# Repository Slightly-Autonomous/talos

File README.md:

# Talos

An open-source, **local-first spatial security and automation platform** for houses and other properties.

- Modular battery/solar sensor nodes: an ESP32-H2-class controller with four coplanar sensor-module slots.
- A local hub that owns all events, state, rules and commands, and works without internet.
- A deterministic digital twin that runs the real production logic in CI.
- A website (PWA first). Optional cloud and observability are never in the alarm path.

> **Status: Phase 8 started (hardware bring-up prep).** Contracts, domain core, an L1 twin (29 scenarios), `talos_hub` (SQLite journal, HTTP API with live events, token auth, optional Supabase copy, Docker/Railway deploys), and a website with live floor plan, replay, engineering, simulation, plus layout and rule editors over versioned, journaled configuration, backed by browser E2E; portable device firmware (drivers, debounce, retry, power admission, A/B OTA) tested on a register-level virtual board against the real hub, and compiled for ESP32-H2 in CI; CoAP device ingress with HMAC-authenticated frames, Ed25519-signed OTA campaigns delivered end to end to virtual nodes, device health projection, metrics and an optional Prometheus/Grafana profile; Supabase sign-in, an MCP server for AI assistants (policy-capped, no unlock/disarm), a webhook notifier and a Frigate NVR connector; a dev-kit bring-up guide, HIL test suite and manufacturing release checklist ready for the first real hardware. Nothing has run on real hardware or a real Thread network yet. See [roadmap](#roadmap). Everything is experimental and is not a certified alarm or life-safety system.

## Quick start

Prerequisites: [bazelisk](https://github.com/bazelbuild/bazelisk), a C++20 compiler (Apple clang 17 / GCC 13+), Node ≥ 20.19 and pnpm 10.

```bash
bazel test //...                    # all C++ tests
```

```bash
bazel test --config=asan //...      # under AddressSanitizer (also: --config=ubsan)
```

```bash
pnpm install && pnpm ts:check       # proto codegen + all TS typecheck/tests + web lint/build
```

```bash
pnpm proto:lint                     # buf lint on contracts/proto
```

```bash
bazel run //server:talos_hub -- --config $PWD/deploy/config/hub.dev.yaml   # then: curl localhost:8080/v1/health
```

See [`deploy/README.md`](deploy/README.md) for Docker Compose, Supabase and Railway.

Run the website against that hub, with virtual devices (log in with `dev-owner-token`):

```bash
pnpm --filter @talos/devsim start
```

```bash
pnpm -C web dev                     # http://localhost:5173
```

```bash
pnpm -C web e2e                     # browser E2E: boots hub + devsim + web itself
```

```bash
bazel run //simulation/runner:talos_sim -- $PWD/simulation/scenarios/scenarios/backyard_intrusion_at_2am.yaml --root $PWD/simulation/scenarios
```

## Repository map
| Path | What |
|---|---|
| `contracts/proto/talos/v1` | Protobuf contracts (the wire/storage schema) |
| `contracts/manifests` | Sample board/module/property YAML. **All numbers provisional** |
| `core/` | Pure C++20 domain core: journal, ingest/dedup, state/replay, commands, policy, rules, manifest validator |
| `codec/` | Proto ↔ core mapping and the YAML loader |
| `simulation/` | Digital twin: world, virtual devices/transport, scenario runner, scenario corpus |
| `server/` | `talos_hub`: SQLite journal, HTTP API v1 + SSE, auth, config switches |
| `packages/contracts` | Generated TypeScript contracts and typed `HubClient` |
| `connectors/supabase_sync` | Optional read-only Supabase copy |
| `connectors/mcp_server` | MCP server for AI assistants (agent principal, policy-capped) |
| `connectors/webhook_notifier` | `notify` commands → ntfy/JSON webhooks |
| `connectors/frigate` | Frigate NVR detections → camera observations |
| `deploy/` | Dev config, Docker Compose, Railway templates, Supabase migrations |
| `web/` | React + TypeScript website: live floor plan, replay, engineering, simulation (Playwright E2E) |
| `tools/devsim` | Virtual devices for the dev property, over the hub's device API |
| `docs/` | Architecture, ADRs, open decisions, security invariants, requirements, original spec |
| `firmware/` | Portable device firmware, virtual board (L2 twin), ESP32-H2 project |
| `common/` | Shared portable code (SHA-256/HMAC, CoAP codec) |
| `hardware/` | Provisional BOMs (dev-kit rig, mainboard candidates); KiCad later |
| `tests/hil/` | Hardware-in-the-loop tests (pytest-embedded, manual workflow) |
| `observability/` | Placeholder (profile lives in `deploy/observability`) |

API reference: [`docs/api.md`](docs/api.md). Start with [`docs/architecture/overview.md`](docs/architecture/overview.md) and [`docs/decisions/`](docs/decisions/README.md).

## Roadmap
0–1. Repo, contracts, deterministic core
2. Deterministic L1 digital twin and scenario runner
3. Local hub: SQLite journal, API, auth
4. Website: live state, replay; 4b: versioned config, layout and rule editors
5. Portable firmware on virtual hardware, then ESP-IDF
6. Thread/CoAP, OTA, observability, hardening
7. Optional Supabase/Railway, MCP connector
8. Dev-board validation, custom PCB, manufacturing ← *here* (needs real hardware)

## License
Apache-2.0. See [LICENSE](LICENSE).

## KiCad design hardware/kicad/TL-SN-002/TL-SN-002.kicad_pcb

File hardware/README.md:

# hardware

The Talos custom-hardware workstream. It follows `TALOS_CUSTOM_HARDWARE_HANDOFF_v0_1` (milestones H0–H7). Root ADRs in `docs/decisions/` still win over anything here (ADR 0017 links the two).

> **Nothing in this folder is a validated design.** The schematics pass ERC and the autorouted layouts pass DRC, but no electrical engineer has reviewed them, and nothing has been built or measured. **Do not order boards** until the review items in [layout/README.md](layout/README.md) are closed (HW-0005). Every value is `provisional: true` until a bench measurement says otherwise.

## Boards

| ID | What | Bespoke? | State |
|---|---|---|---|
| TL-HUB-REF | Hub: Pi 5 / mini-PC + USB 802.15.4 RCP | No, bought | `bom/devkit_rig_v0.csv` |
| TL-SN-002 | Self-contained Thread Sensor Node: ESP32-H2, Hall + accel + T/RH + PIR, 2 × AA or USB-C, 10 lamps, 3 buttons (ADR 0019) | Yes | Schematic + routed 2-layer layout, 0 DRC errors, not yet reviewed |
| TL-SN-001, TL-MOD-001..004, TL-TEST-001 | The four-slot modular node and its cards | – | **Archived** 2026-11-22: [archive/modular-2026-11](archive/modular-2026-11/README.md) (git tag `modular-checkpoint-2026-11`) |
| TL-DBG-001 | One-slot USB debug adapter: one sensor_edge_v1 board on a PC, kept active for future sensor boards (MCP2221A bridge, PPK2 meter headers) | Yes, bench tool | Schematic + routed 2-layer layout, 0 DRC errors ([HW-0007](architecture/decisions/0007-slot-socket-and-debug-adapter.md)) |
| TL-VN-001 | Vision Node (separate board, CM4/CM5/video SoC) | Yes | H5 study not started; manifest only |

The camera **slot** module (`smart_camera_s3_v1`) is superseded by TL-VN-001 ([ADR HW-0001](architecture/decisions/0001-hardware-family.md)).

## Where things are

| Path | Contents |
|---|---|
| `architecture/` | [hardware-overview.md](architecture/hardware-overview.md) and hardware ADRs HW-0001..0006 |
| `requirements/` | Requirements (`hardware-requirements.yaml`), decision/risk register, datasheet register, component selection, interface test matrix |
| `interfaces/` | [sensor_edge_v1](interfaces/sensor_edge_v1.md) slot connector contract |
| `pins/` | Complete ESP32-H2-MINI-1 pad ledger (CSV), the single source for the firmware `BoardSupport` table |
| `budgets/` | Per-slot and board resource budget (CSV) |
| `power/` | Power-tree study and operating-mode matrix (H2) |
| `mechanical/` | Connector shortlist and mechanical notes |
| `kicad/` | KiCad 10 projects, all **generated** by `scripts/gen_schematics.py`; project-local symbols in `kicad/libraries/` |
| `scripts/` | Schematic generator, ERC/netlist checks, power-budget calculator |
| `results/` | Captured tool output (ERC/DRC summary, netlist comparison, power report), dated and versioned |
| `layout/` | H4 layout method, board summary and the pre-order review list |
| `fab/` | Prototype fabrication packages (Gerbers, drill, CPL, BOM, renders), for quotes and DFM only |
| `templates/` | Component evaluation template |
| `bom/` | Dev-kit rig BOM (bring-up path, ADR 0016) |

Board and module manifests live in `contracts/manifests/` (one schema, validated by `core/manifest`). `sensor_node_proto_a.yaml` must agree with `pins/esp32h2_mini1_pin_ledger.csv` and `firmware/esp_idf/main/board_tl_sn_001.h`.

## Reproduce

```bash
# KiCad 10.0.x: kicad-cli on PATH, or set KICAD_CLI.
python3 hardware/scripts/gen_schematics.py          # regenerate all projects
python3 hardware/scripts/check_kicad.py --pdf      # ERC + netlist round-trip + PDFs -> hardware/results/
python3 hardware/scripts/power_budget.py             # H2 calculations -> hardware/results/power-budget.md
bazel test //core/manifest:manifest_test //codec:yaml_loader_test   # manifest validator (HW-MF tests)
```

## Hard rules
- Do not order parts or boards, request binding quotes, create factory keys or burn eFuses without explicit owner approval.
- Never hand-edit a generated `.kicad_sch`. Change the generator, regenerate, and re-run the checks.
- A green ERC is not "validated". See `requirements/design-risks.md` for what still needs a reviewer or a bench.

Vendor drawings marked proprietary (e.g. Samtec's HSEC8 prints) live in `hardware/vendor-docs/`, which git ignores. Re-download them from the vendor site; the register in `requirements/datasheet-register.md` names each one.

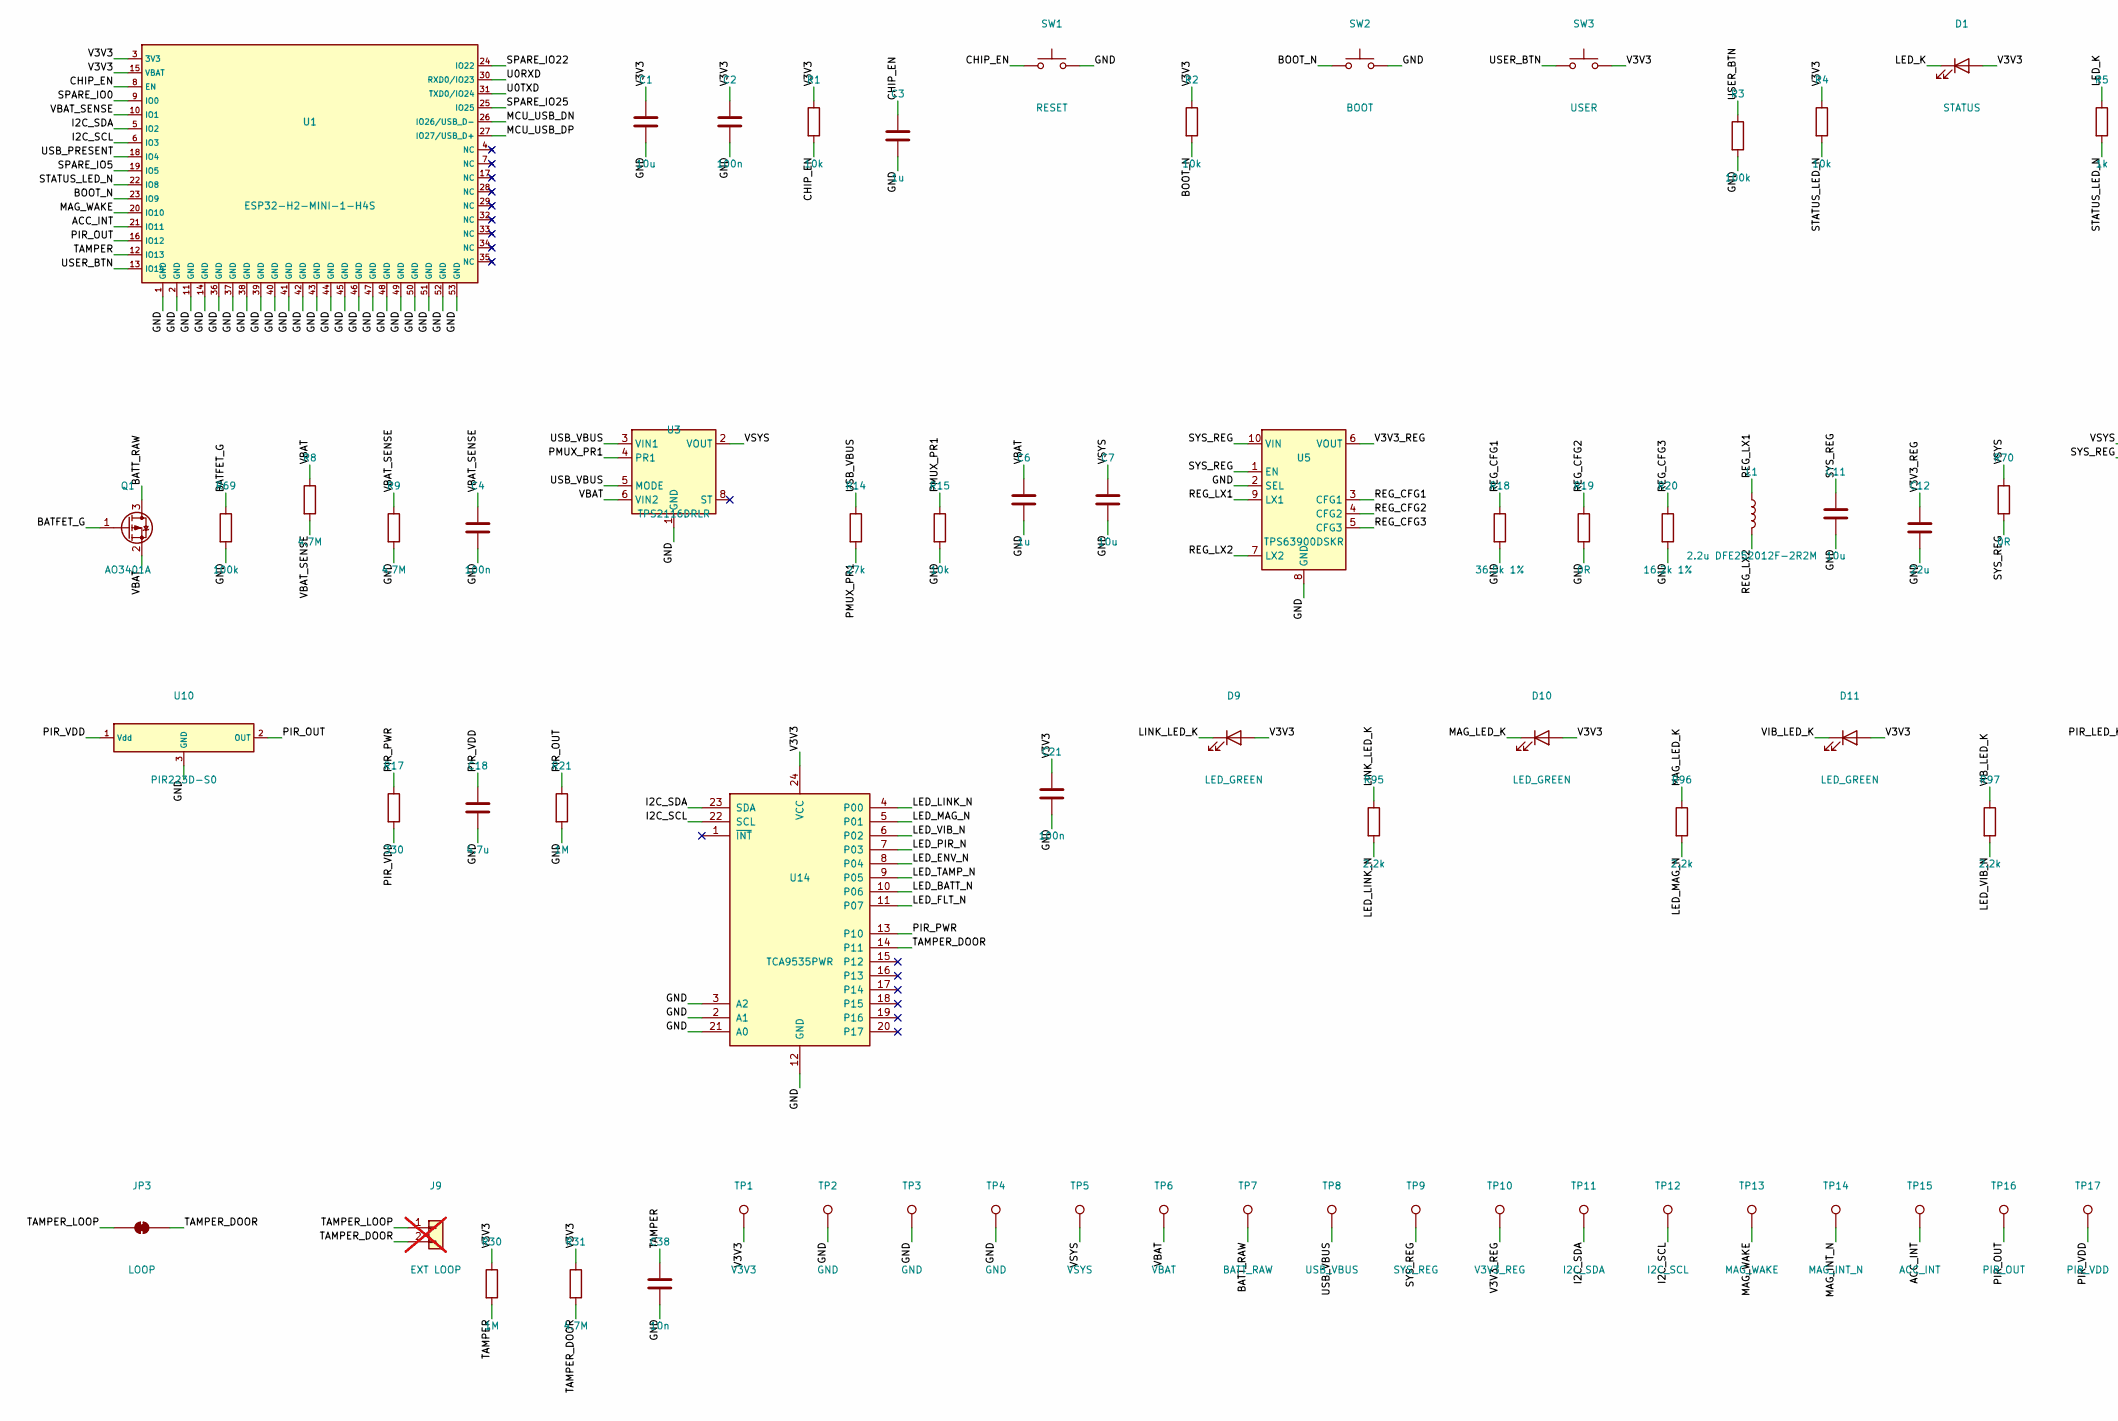
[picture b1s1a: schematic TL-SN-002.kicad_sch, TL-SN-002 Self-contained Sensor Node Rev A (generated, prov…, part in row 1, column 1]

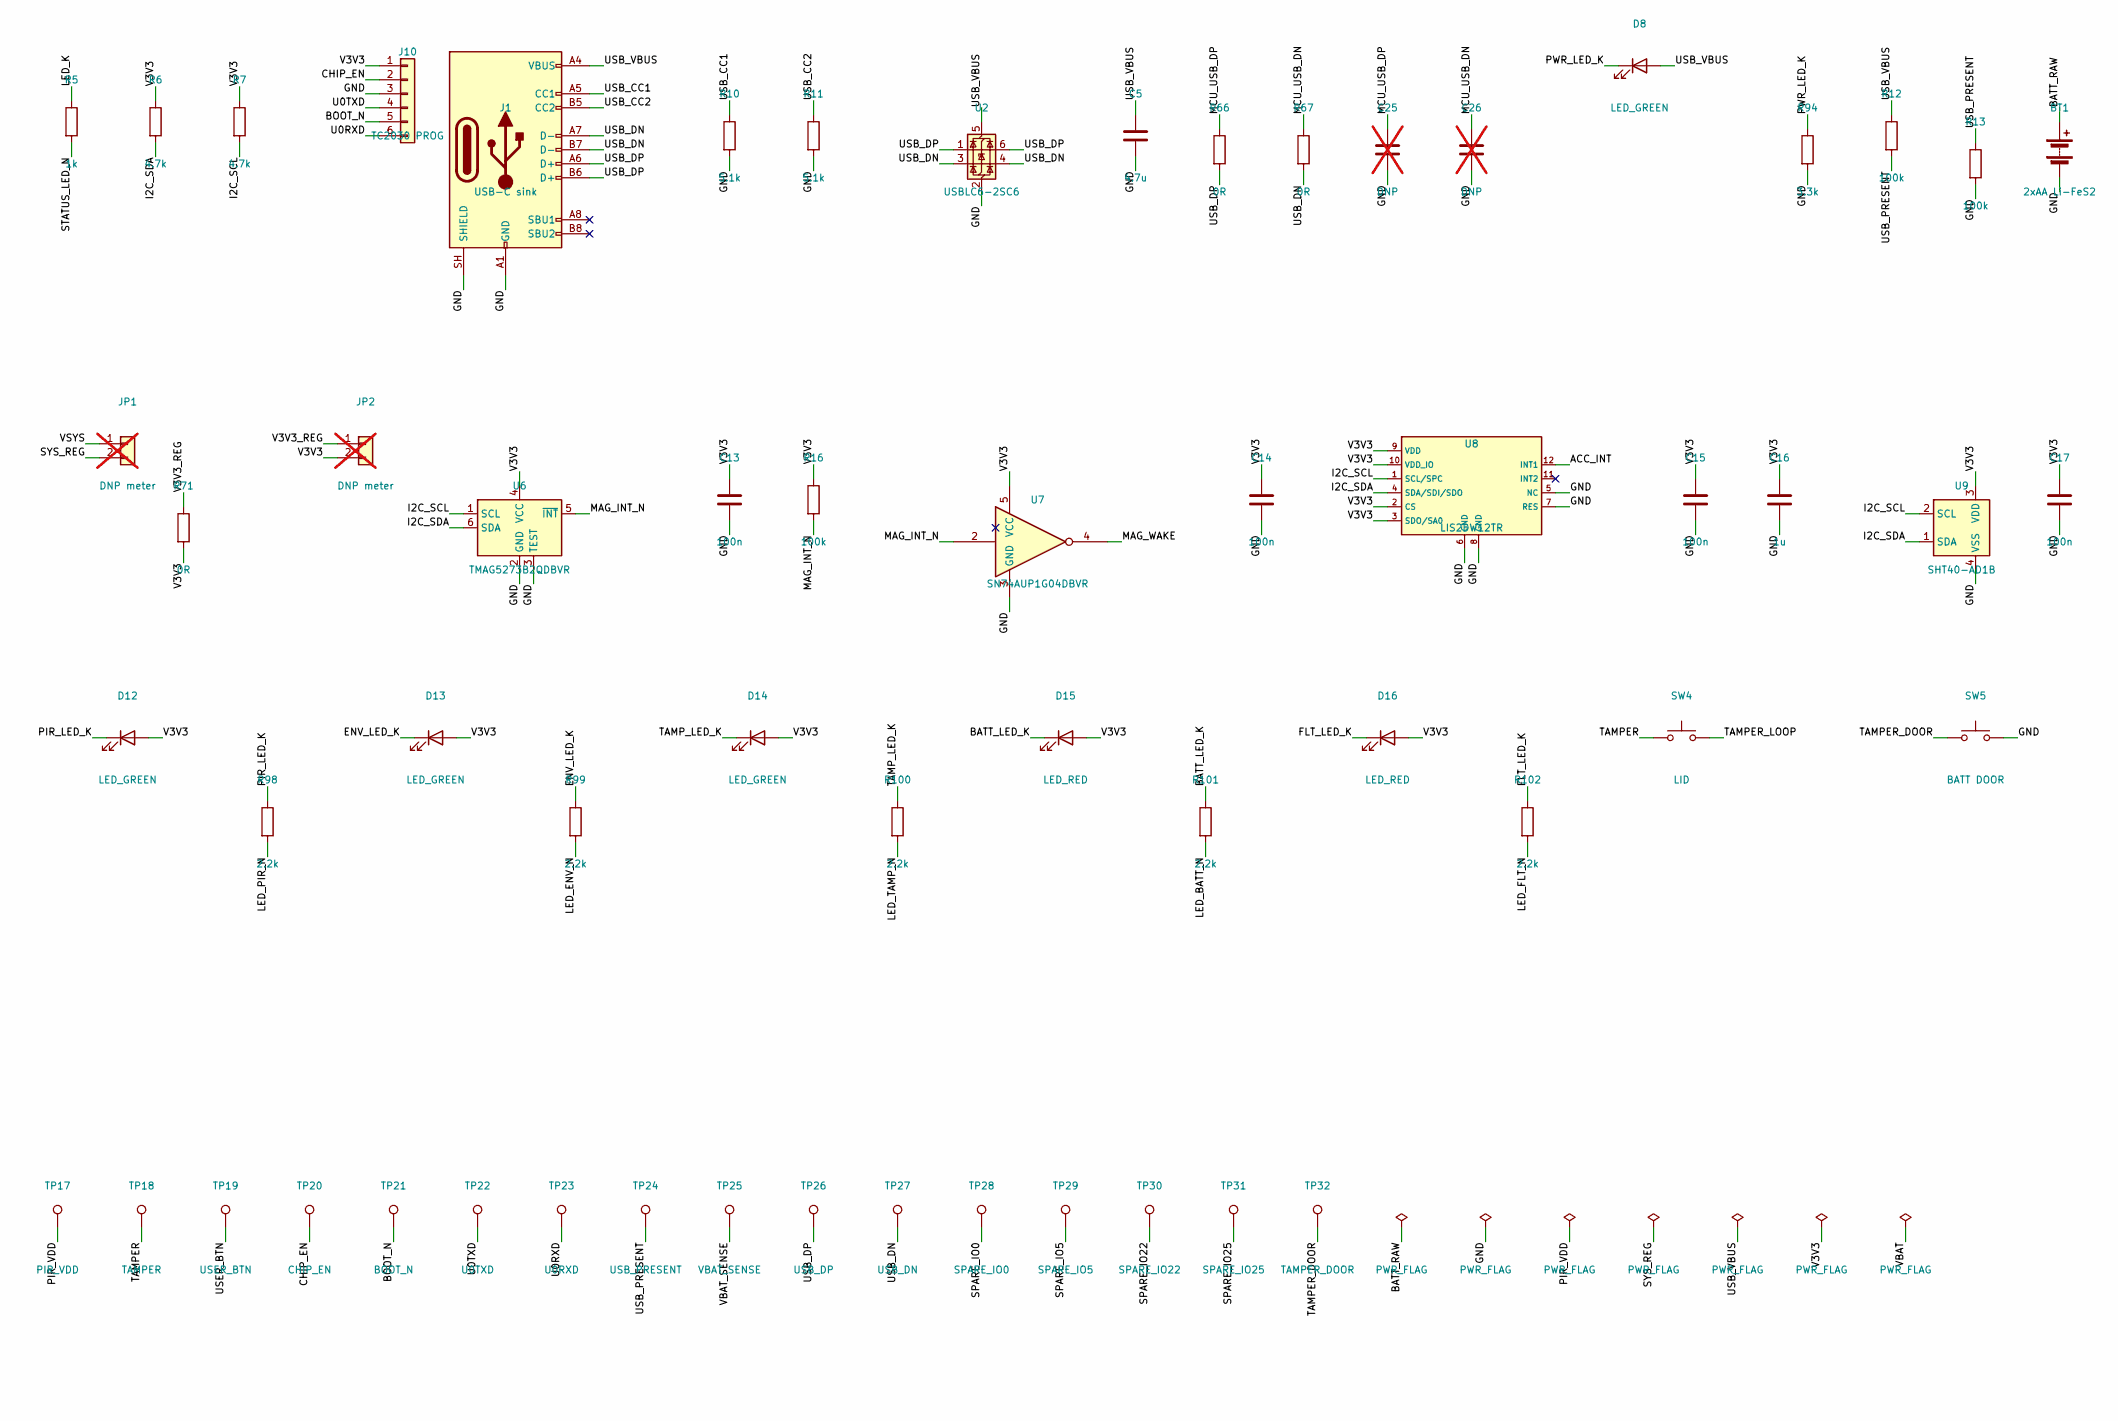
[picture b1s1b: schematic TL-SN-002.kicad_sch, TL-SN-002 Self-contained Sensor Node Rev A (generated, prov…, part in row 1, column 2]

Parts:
BT1: 2xAA Li-FeS2; BatteryHolder_Keystone_2462_2xAA
C1, C7, C11: 10u; C_0805_2012Metric
C2, C4, C13, C14, C15, C17, C21: 100n; C_0402_1005Metric
C3, C6, C16: 1u; C_0402_1005Metric
C5, C18: 4.7u; C_0805_2012Metric
C12: 22u; C_0805_2012Metric
C25, C26: DNP; C_0402_1005Metric; not fitted
C38: 10n; C_0402_1005Metric
D1: STATUS; LED_0603_1608Metric
D8, D9, D10, D11, D12, D13, D14: LED_GREEN; LED_0603_1608Metric
D15, D16: LED_RED; LED_0603_1608Metric
J1: USB-C sink; USB_C_Receptacle_GCT_USB4105-xx-A_16P_TopMnt_Horizontal
J9: EXT LOOP; JST_PH_S2B-PH-SM4-TB_1x02-1MP_P2.00mm_Horizontal; not fitted
J10: TC2030 PROG; Tag-Connect_TC2030-IDC-NL_2x03_P1.27mm_Vertical
JP1, JP2: DNP meter; PinHeader_1x02_P2.54mm_Vertical; not fitted
JP3: LOOP; SolderJumper-2_P1.3mm_Bridged_RoundedPad1.0x1.5mm
L1: 2.2u DFE252012F-2R2M; L_1008_2520Metric
Q1: AO3401A; SOT-23
R1, R2, R4, R15: 10k; R_0402_1005Metric
R3, R12, R13, R16, R69: 100k; R_0402_1005Metric
R5: 1k; R_0402_1005Metric
R6, R7: 4.7k; R_0402_1005Metric
R8, R9, R31: 4.7M; R_0402_1005Metric
R10, R11: 5.1k; R_0402_1005Metric
R14: 27k; R_0402_1005Metric
R17: 330; R_0402_1005Metric
R18: 36.5k 1%; R_0402_1005Metric
R19, R66, R67: 0R; R_0402_1005Metric
R20: 16.2k 1%; R_0402_1005Metric
R21, R30: 1M; R_0402_1005Metric
R70, R71: 0R; R_0805_2012Metric
R94: 3.3k; R_0402_1005Metric
R95, R96, R97, R98, R99, R100, R101, R102: 2.2k; R_0402_1005Metric
SW1: RESET; SW_SPST_PTS810
SW2: BOOT; SW_SPST_PTS810
SW3: USER; SW_SPST_PTS810
SW4: LID; SW_Push_1P1T_XKB_TS-1187A
SW5: BATT DOOR; SW_Push_1P1T_XKB_TS-1187A
TP1: V3V3; TestPoint_Pad_D1.0mm
TP2, TP3, TP4: GND; TestPoint_Pad_D1.0mm
TP5: VSYS; TestPoint_Pad_D1.0mm
TP6: VBAT; TestPoint_Pad_D1.0mm
TP7: BATT_RAW; TestPoint_Pad_D1.0mm
TP8: USB_VBUS; TestPoint_Pad_D1.0mm
TP9: SYS_REG; TestPoint_Pad_D1.0mm
TP10: V3V3_REG; TestPoint_Pad_D1.0mm
TP11: I2C_SDA; TestPoint_Pad_D1.0mm
TP12: I2C_SCL; TestPoint_Pad_D1.0mm
TP13: MAG_WAKE; TestPoint_Pad_D1.0mm
TP14: MAG_INT_N; TestPoint_Pad_D1.0mm
TP15: ACC_INT; TestPoint_Pad_D1.0mm
TP16: PIR_OUT; TestPoint_Pad_D1.0mm
TP17: PIR_VDD; TestPoint_Pad_D1.0mm
TP18: TAMPER; TestPoint_Pad_D1.0mm
TP19: USER_BTN; TestPoint_Pad_D1.0mm
TP20: CHIP_EN; TestPoint_Pad_D1.0mm
TP21: BOOT_N; TestPoint_Pad_D1.0mm
TP22: U0TXD; TestPoint_Pad_D1.0mm
TP23: U0RXD; TestPoint_Pad_D1.0mm
TP24: USB_PRESENT; TestPoint_Pad_D1.0mm
TP25: VBAT_SENSE; TestPoint_Pad_D1.0mm
TP26: USB_DP; TestPoint_Pad_D1.0mm
TP27: USB_DN; TestPoint_Pad_D1.0mm
TP28: SPARE_IO0; TestPoint_Pad_D1.0mm
TP29: SPARE_IO5; TestPoint_Pad_D1.0mm
TP30: SPARE_IO22; TestPoint_Pad_D1.0mm
TP31: SPARE_IO25; TestPoint_Pad_D1.0mm
TP32: TAMPER_DOOR; TestPoint_Pad_D1.0mm
U1: ESP32-H2-MINI-1-H4S; ESP32-H2-MINI-1
U2: USBLC6-2SC6; SOT-23-6
U3: TPS2116DRLR; SOT-583-8
U5: TPS63900DSKR; WSON-10-1EP_2.5x2.5mm_P0.5mm_EP1.2x2mm
U6: TMAG5273B2QDBVR; SOT-23-6
U7: SN74AUP1G04DBVR; SOT-23-5
U8: LIS2DW12TR; LGA-12_2x2mm_P0.5mm
U9: SHT40-AD1B; Sensirion_DFN-4_1.5x1.5mm_P0.8mm_SHT4x_CentralKeepout
U10: PIR223D-S0; PIR_NEWOPTO_PIR223D_TO-5
U14: TCA9535PWR; TSSOP-24_4.4x7.8mm_P0.65mm

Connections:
/ACC_INT: TP15.1, U1.21 (IO11), U8.12 (INT1)
/BATFET_G: Q1.1 (G), R69.1
/BATT_LED_K: D15.1 (K), R101.1
/BATT_RAW: BT1.1 (+), Q1.3 (D), TP7.1
/BOOT_N: J10.5, R2.2, SW2.1, TP21.1, U1.23 (IO9)
/CHIP_EN: C3.1, J10.2, R1.2, SW1.1, TP20.1, U1.8 (EN)
/ENV_LED_K: D13.1 (K), R99.1
/FLT_LED_K: D16.1 (K), R102.1
/GND: BT1.2 (-), C1.2, C2.2, C3.2, C4.2, C5.2, C6.2, C7.2, C11.2, C12.2, C13.2, C14.2, C15.2, C16.2, C17.2, C18.2, C21.2, C25.2, C26.2, C38.2, J1.A1 (GND), J1.A12 (GND), J1.B1 (GND), J1.B12 (GND), J1.SH (SHIELD), J10.3, R3.2, R9.2, R10.2, R11.2, R13.2, R15.2, R18.2, R19.2, R20.2, R21.2, R69.2, R94.2, SW1.2, SW2.2, SW5.2, TP2.1, TP3.1, TP4.1, U1.1 (GND), U1.2 (GND), U1.11 (GND), U1.14 (GND), U1.36 (GND), U1.37 (GND), U1.38 (GND), U1.39 (GND), U1.40 (GND), U1.41 (GND), U1.42 (GND), U1.43 (GND), U1.44 (GND), U1.45 (GND), U1.46 (GND), U1.47 (GND), U1.48 (GND), U1.49 (GND), U1.50 (GND), U1.51 (GND), U1.52 (GND), U1.53 (GND), U2.2 (GND), U3.1 (GND), U5.2 (SEL), U5.8 (GND), U5.11 (GND), U6.2 (GND), U6.3 (TEST), U7.3 (GND), U8.5 (NC), U8.6 (GND), U8.7 (RES), U8.8 (GND), U9.4 (VSS), U10.3 (GND), U14.2 (A1), U14.3 (A2), U14.12 (GND), U14.21 (A0)
/I2C_SCL: R7.2, TP12.1, U1.6 (IO3), U6.1 (SCL), U8.1 (SCL/SPC), U9.2 (SCL), U14.22 (SCL)
/I2C_SDA: R6.2, TP11.1, U1.5 (IO2), U6.6 (SDA), U8.4 (SDA/SDI/SDO), U9.1 (SDA), U14.23 (SDA)
/LED_BATT_N: R101.2, U14.10 (P06)
/LED_ENV_N: R99.2, U14.8 (P04)
/LED_FLT_N: R102.2, U14.11 (P07)
/LED_K: D1.1 (K), R5.1
/LED_LINK_N: R95.2, U14.4 (P00)
/LED_MAG_N: R96.2, U14.5 (P01)
/LED_PIR_N: R98.2, U14.7 (P03)
/LED_TAMP_N: R100.2, U14.9 (P05)
/LED_VIB_N: R97.2, U14.6 (P02)
/LINK_LED_K: D9.1 (K), R95.1
/MAG_INT_N: R16.2, TP14.1, U6.5 (~INT), U7.2
/MAG_LED_K: D10.1 (K), R96.1
/MAG_WAKE: TP13.1, U1.20 (IO10), U7.4
/MCU_USB_DN: C26.1, R67.1, U1.26 (IO26/USB_D-)
/MCU_USB_DP: C25.1, R66.1, U1.27 (IO27/USB_D+)
/PIR_LED_K: D12.1 (K), R98.1
/PIR_OUT: R21.1, TP16.1, U1.16 (IO12), U10.2 (OUT)
/PIR_PWR: R17.1, U14.13 (P10)
/PIR_VDD: C18.1, R17.2, TP17.1, U10.1 (Vdd)
/PMUX_PR1: R14.2, R15.1, U3.4 (PR1)
/PWR_LED_K: D8.1 (K), R94.1
/REG_CFG1: R18.1, U5.3 (CFG1)
/REG_CFG2: R19.1, U5.4 (CFG2)
/REG_CFG3: R20.1, U5.5 (CFG3)
/REG_LX1: L1.1, U5.9 (LX1)
/REG_LX2: L1.2, U5.7 (LX2)
/SPARE_IO0: TP28.1, U1.9 (IO0)
/SPARE_IO5: TP29.1, U1.19 (IO5)
/SPARE_IO22: TP30.1, U1.24 (IO22)
/SPARE_IO25: TP31.1, U1.25 (IO25)
/STATUS_LED_N: R4.2, R5.2, U1.22 (IO8)
/SYS_REG: C11.1, JP1.2, R70.2, TP9.1, U5.1 (EN), U5.10 (VIN)
/TAMPER: C38.1, R30.2, SW4.1, TP18.1, U1.12 (IO13)
/TAMPER_DOOR: J9.2, JP3.2 (B), R31.2, SW5.1, TP32.1, U14.14 (P11)
/TAMPER_LOOP: J9.1, JP3.1 (A), SW4.2
/TAMP_LED_K: D14.1 (K), R100.1
/U0RXD: J10.6, TP23.1, U1.30 (RXD0/IO23)
/U0TXD: J10.4, TP22.1, U1.31 (TXD0/IO24)
/USB_CC1: J1.A5 (CC1), R10.1
/USB_CC2: J1.B5 (CC2), R11.1
/USB_DN: J1.A7 (D-), J1.B7 (D-), R67.2, TP27.1, U2.3 (I/O2), U2.4 (I/O2)
/USB_DP: J1.A6 (D+), J1.B6 (D+), R66.2, TP26.1, U2.1 (I/O1), U2.6 (I/O1)
/USB_PRESENT: R12.2, R13.1, TP24.1, U1.18 (IO4)
/USB_VBUS: C5.1, D8.2 (A), J1.A4 (VBUS), J1.A9 (VBUS), J1.B4 (VBUS), J1.B9 (VBUS), R12.1, R14.1, TP8.1, U2.5 (VBUS), U3.3 (VIN1), U3.5 (MODE)
/USER_BTN: R3.1, SW3.1, TP19.1, U1.13 (IO14)
/V3V3: C1.1, C2.1, C13.1, C14.1, C15.1, C16.1, C17.1, C21.1, D1.2 (A), D9.2 (A), D10.2 (A), D11.2 (A), D12.2 (A), D13.2 (A), D14.2 (A), D15.2 (A), D16.2 (A), J10.1, JP2.2, R1.1, R2.1, R4.1, R6.1, R7.1, R16.1, R30.1, R31.1, R71.2, SW3.2, TP1.1, U1.3 (3V3), U1.15 (VBAT), U6.4 (VCC), U7.5 (VCC), U8.2 (CS), U8.3 (SDO/SA0), U8.9 (VDD), U8.10 (VDD_IO), U9.3 (VDD), U14.24 (VCC)
/V3V3_REG: C12.1, JP2.1, R71.1, TP10.1, U5.6 (VOUT)
/VBAT: C6.1, Q1.2 (S), R8.1, TP6.1, U3.6 (VIN2)
/VBAT_SENSE: C4.1, R8.2, R9.1, TP25.1, U1.10 (IO1)
/VIB_LED_K: D11.1 (K), R97.1
/VSYS: C7.1, JP1.1, R70.1, TP5.1, U3.2 (VOUT), U3.7 (VOUT)

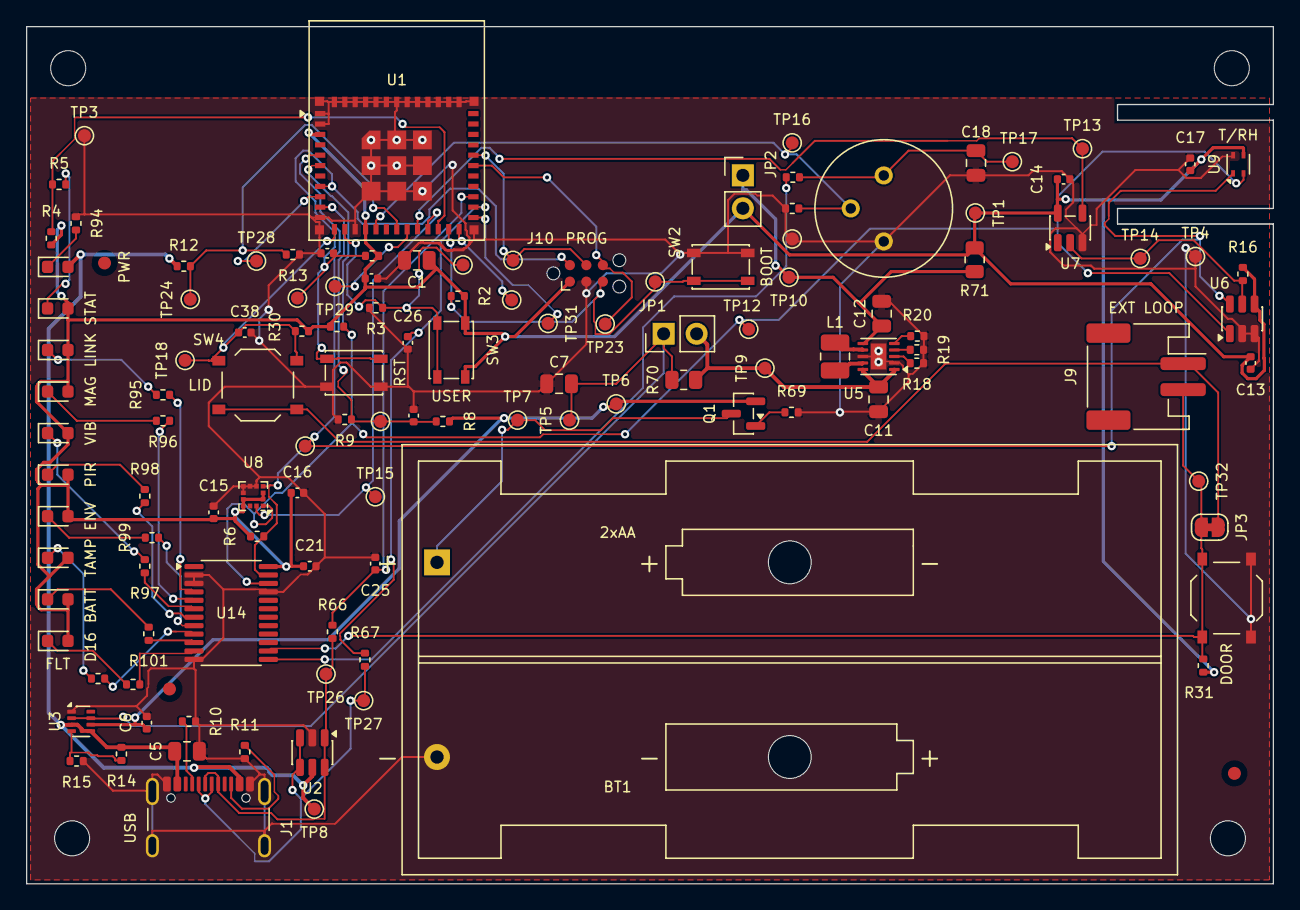
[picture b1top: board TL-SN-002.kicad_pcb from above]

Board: 2 copper layers, 96.0 x 66.0 mm, 129 parts (0 on the bottom side), 62 nets.

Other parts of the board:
FID1, FID2, FID3: fiducial; Fiducial_1mm_Mask2mm
H1, H2, H3, H4: mounting hole; MountingHole_2.7mm_M2.5

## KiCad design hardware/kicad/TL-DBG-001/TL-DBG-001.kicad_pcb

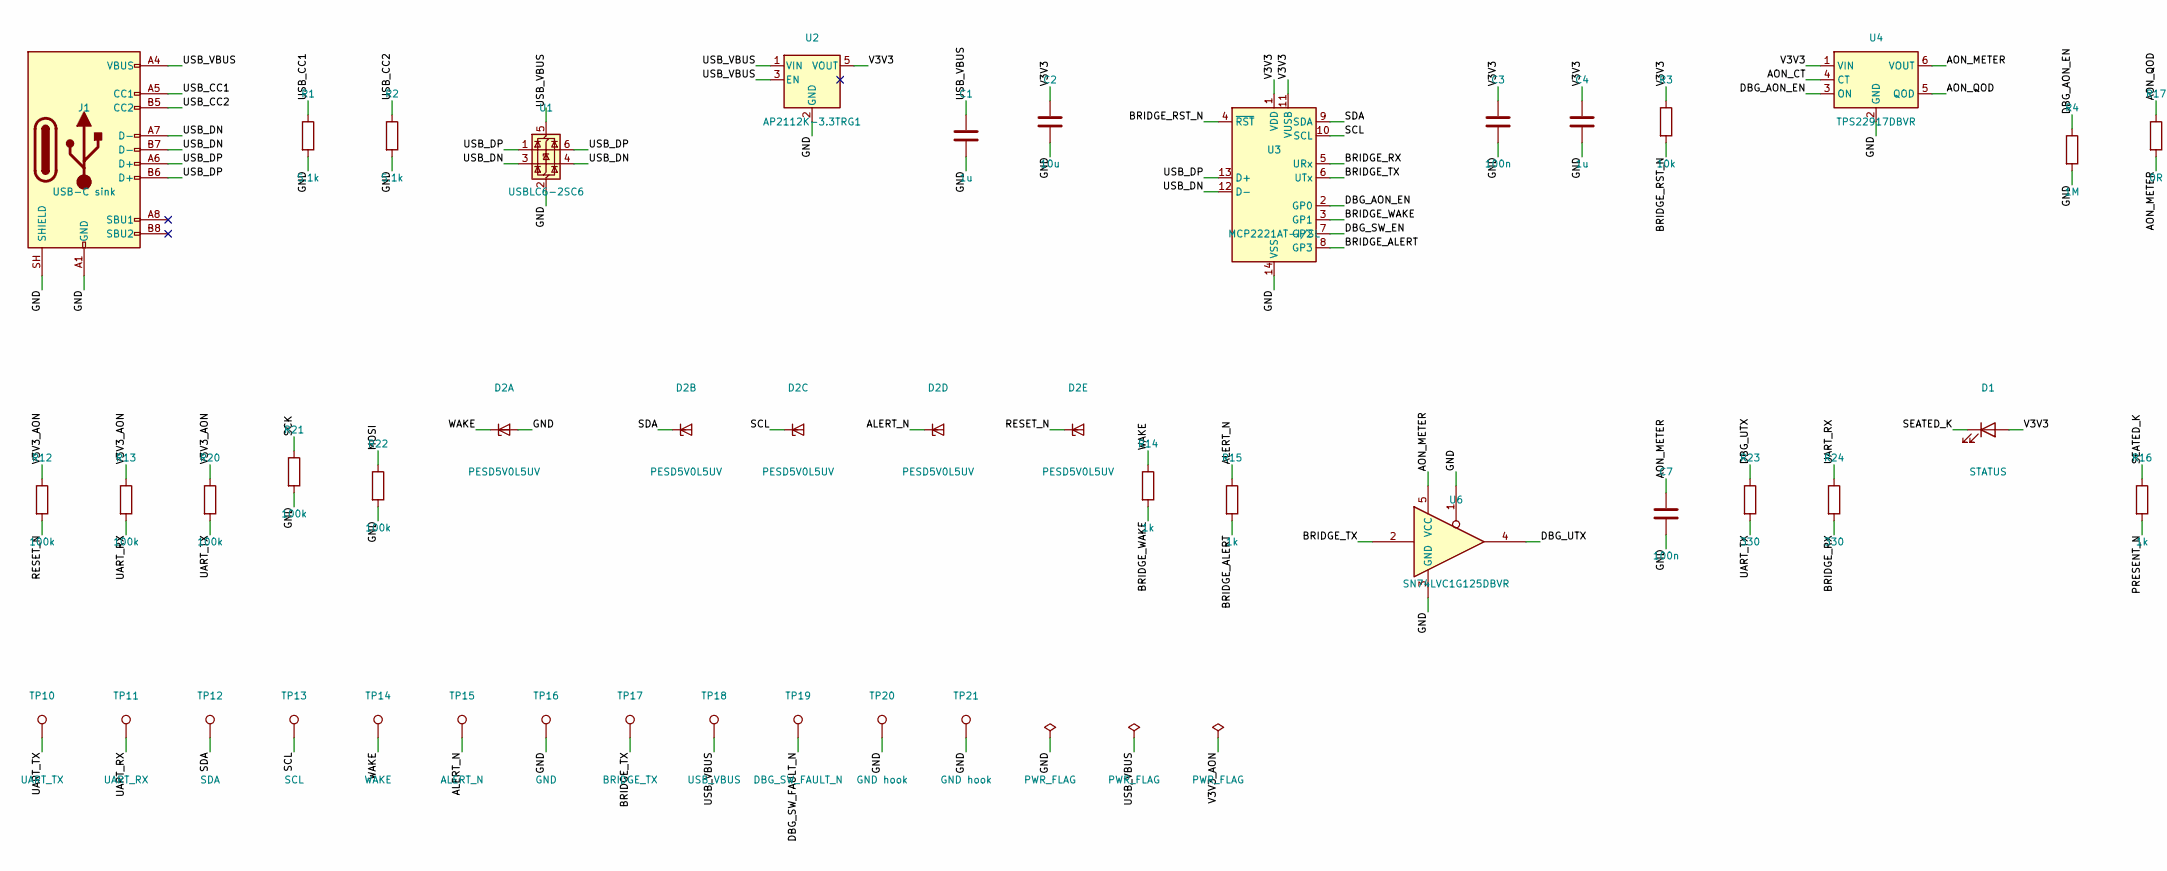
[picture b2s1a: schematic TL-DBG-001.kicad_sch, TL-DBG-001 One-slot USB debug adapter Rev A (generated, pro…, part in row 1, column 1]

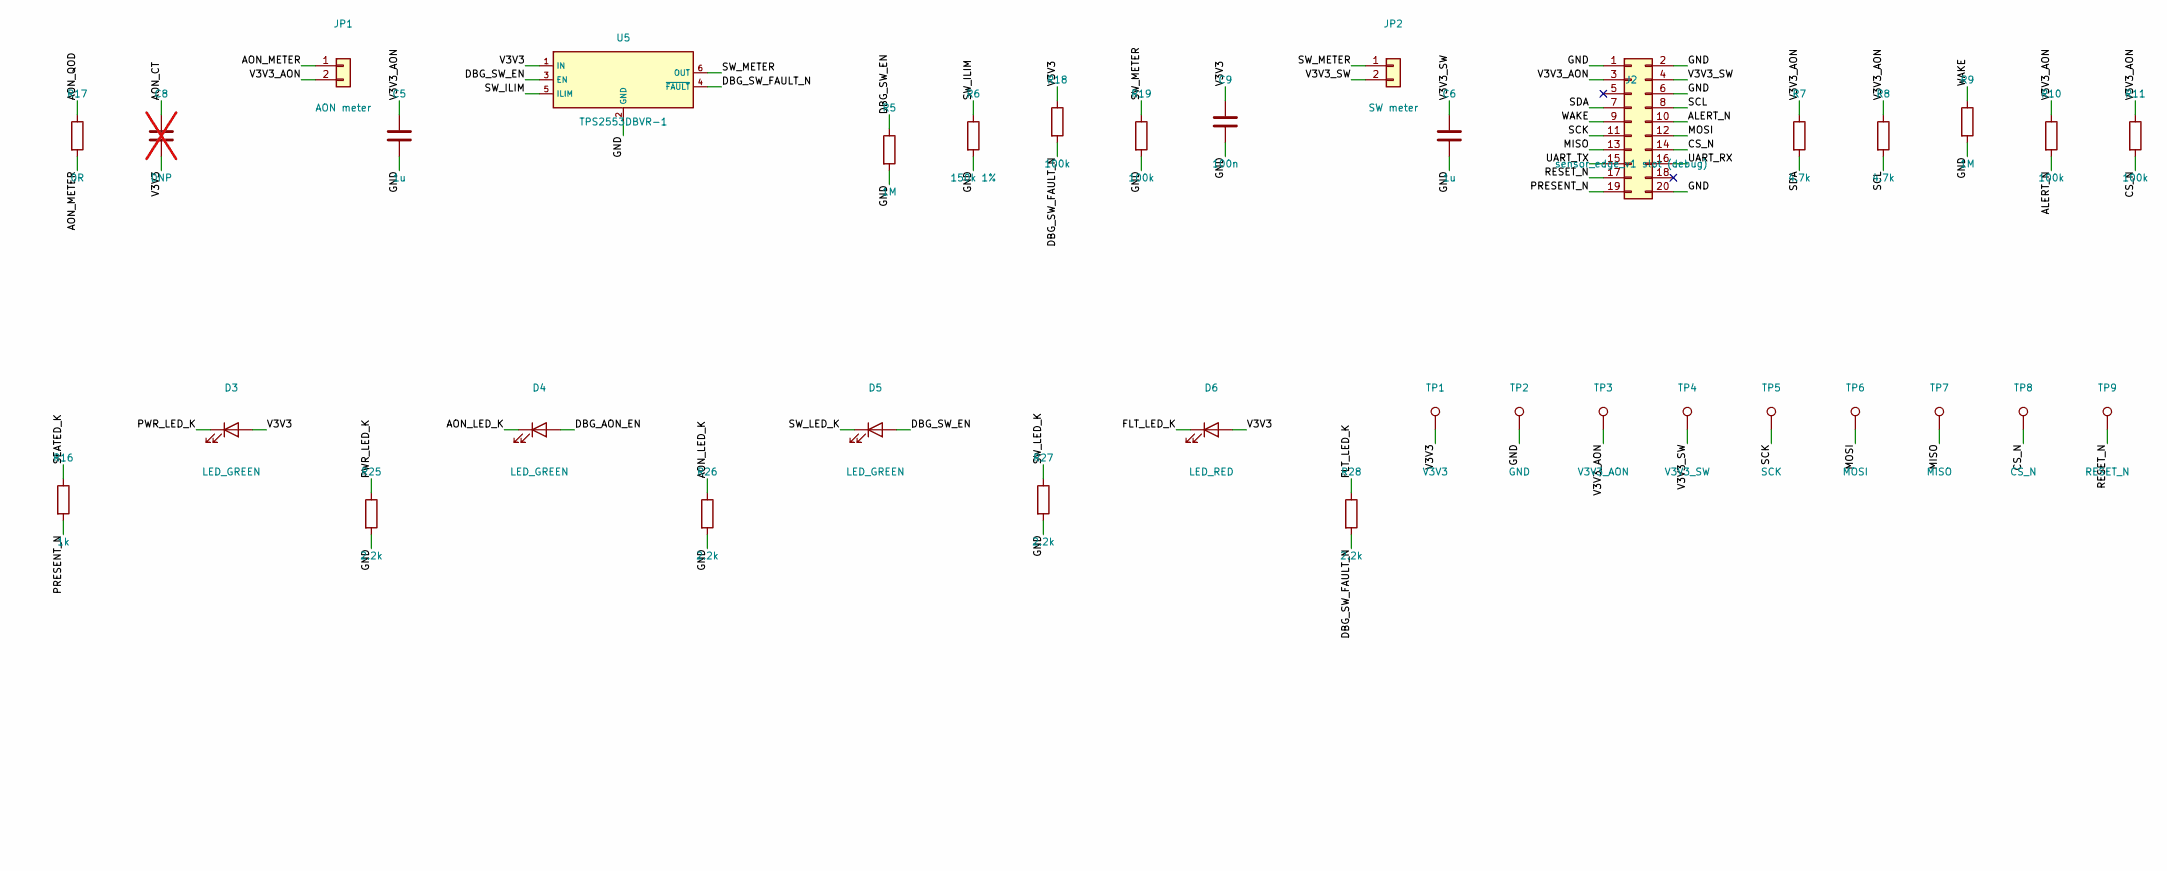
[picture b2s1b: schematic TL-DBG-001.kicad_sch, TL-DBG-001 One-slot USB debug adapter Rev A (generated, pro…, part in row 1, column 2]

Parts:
C1, C4, C5, C6: 1u; C_0402_1005Metric
C2: 10u; C_0805_2012Metric
C3, C7, C9: 100n; C_0402_1005Metric
C8: DNP; C_0402_1005Metric; not fitted
D1: STATUS; LED_0603_1608Metric
D2: PESD5V0L5UV; SOT-666
D3, D4, D5: LED_GREEN; LED_0603_1608Metric
D6: LED_RED; LED_0603_1608Metric
J1: USB-C sink; USB_C_Receptacle_GCT_USB4105-xx-A_16P_TopMnt_Horizontal
J2: sensor_edge_v1 slot (debug); Samtec_HSEC8-110-01-S-D-EM2
JP1: AON meter; PinHeader_1x02_P2.54mm_Vertical
JP2: SW meter; PinHeader_1x02_P2.54mm_Vertical
R1, R2: 5.1k; R_0402_1005Metric
R3: 10k; R_0402_1005Metric
R4, R5, R9: 1M; R_0402_1005Metric
R6: 150k 1%; R_0402_1005Metric
R7, R8: 4.7k; R_0402_1005Metric
R10, R11, R12, R13, R18, R19, R20, R21, R22: 100k; R_0402_1005Metric
R14, R15, R16: 1k; R_0402_1005Metric
R17: 0R; R_0402_1005Metric
R23, R24: 330; R_0402_1005Metric
R25, R26, R27, R28: 2.2k; R_0402_1005Metric
TP1: V3V3; TestPoint_Pad_D1.0mm
TP2, TP16: GND; TestPoint_Pad_D1.0mm
TP3: V3V3_AON; TestPoint_Pad_D1.0mm
TP4: V3V3_SW; TestPoint_Pad_D1.0mm
TP5: SCK; TestPoint_Pad_D1.0mm
TP6: MOSI; TestPoint_Pad_D1.0mm
TP7: MISO; TestPoint_Pad_D1.0mm
TP8: CS_N; TestPoint_Pad_D1.0mm
TP9: RESET_N; TestPoint_Pad_D1.0mm
TP10: UART_TX; TestPoint_Pad_D1.0mm
TP11: UART_RX; TestPoint_Pad_D1.0mm
TP12: SDA; TestPoint_Pad_D1.0mm
TP13: SCL; TestPoint_Pad_D1.0mm
TP14: WAKE; TestPoint_Pad_D1.0mm
TP15: ALERT_N; TestPoint_Pad_D1.0mm
TP17: BRIDGE_TX; TestPoint_Pad_D1.0mm
TP18: USB_VBUS; TestPoint_Pad_D1.0mm
TP19: DBG_SW_FAULT_N; TestPoint_Pad_D1.0mm
TP20, TP21: GND hook; TestPoint_Keystone_5000-5004_Miniature
U1: USBLC6-2SC6; SOT-23-6
U2: AP2112K-3.3TRG1; SOT-23-5
U3: MCP2221AT-I/SL; SOIC-14_3.9x8.7mm_P1.27mm
U4: TPS22917DBVR; SOT-23-6
U5: TPS2553DBVR-1; SOT-23-6
U6: SN74LVC1G125DBVR; SOT-23-5

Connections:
/ALERT_N: D2.5 (K4), J2.10, R10.2, R15.1, TP15.1
/AON_CT: C8.1, U4.4 (CT)
/AON_LED_K: D4.1 (K), R26.1
/AON_METER: C7.1, JP1.1, R17.2, U4.6 (VOUT), U6.5 (VCC)
/AON_QOD: R17.1, U4.5 (QOD)
/BRIDGE_ALERT: R15.2, U3.8 (GP3)
/BRIDGE_RST_N: R3.2, U3.4 (~RST)
/BRIDGE_RX: R24.2, U3.5 (URx)
/BRIDGE_TX: TP17.1, U3.6 (UTx), U6.2
/BRIDGE_WAKE: R14.2, U3.3 (GP1)
/CS_N: J2.14, R11.2, TP8.1
/DBG_AON_EN: D4.2 (A), R4.1, U3.2 (GP0), U4.3 (ON)
/DBG_SW_EN: D5.2 (A), R5.1, U3.7 (GP2), U5.3 (EN)
/DBG_SW_FAULT_N: R18.2, R28.2, TP19.1, U5.4 (~FAULT)
/DBG_UTX: R23.1, U6.4
/FLT_LED_K: D6.1 (K), R28.1
/GND: C1.2, C2.2, C3.2, C4.2, C5.2, C6.2, C7.2, C9.2, D2.2 (A), J1.A1 (GND), J1.A12 (GND), J1.B1 (GND), J1.B12 (GND), J1.SH (SHIELD), J2.1, J2.2, J2.6, J2.20, R1.2, R2.2, R4.2, R5.2, R6.2, R9.2, R19.2, R21.2, R22.2, R25.2, R26.2, R27.2, TP2.1, TP16.1, TP20.1, TP21.1, U1.2 (GND), U2.2 (GND), U3.14 (VSS), U4.2 (GND), U5.2 (GND), U6.1, U6.3 (GND)
/MISO: J2.13, TP7.1
/MOSI: J2.12, R22.1, TP6.1
/PRESENT_N: J2.19, R16.2
/PWR_LED_K: D3.1 (K), R25.1
/RESET_N: D2.6 (K5), J2.17, R12.2, TP9.1
/SCK: J2.11, R21.1, TP5.1
/SCL: D2.4 (K3), J2.8, R8.2, TP13.1, U3.10 (SCL)
/SDA: D2.3 (K2), J2.7, R7.2, TP12.1, U3.9 (SDA)
/SEATED_K: D1.1 (K), R16.1
/SW_ILIM: R6.1, U5.5 (ILIM)
/SW_LED_K: D5.1 (K), R27.1
/SW_METER: JP2.1, R19.1, U5.6 (OUT)
/UART_RX: J2.16, R13.2, R24.1, TP11.1
/UART_TX: J2.15, R20.2, R23.2, TP10.1
/USB_CC1: J1.A5 (CC1), R1.1
/USB_CC2: J1.B5 (CC2), R2.1
/USB_DN: J1.A7 (D-), J1.B7 (D-), U1.3 (I/O2), U1.4 (I/O2), U3.12 (D-)
/USB_DP: J1.A6 (D+), J1.B6 (D+), U1.1 (I/O1), U1.6 (I/O1), U3.13 (D+)
/USB_VBUS: C1.1, J1.A4 (VBUS), J1.A9 (VBUS), J1.B4 (VBUS), J1.B9 (VBUS), TP18.1, U1.5 (VBUS), U2.1 (VIN), U2.3 (EN)
/V3V3: C2.1, C3.1, C4.1, C8.2, C9.1, D1.2 (A), D3.2 (A), D6.2 (A), R3.1, R18.1, TP1.1, U2.5 (VOUT), U3.1 (VDD), U3.11 (VUSB), U4.1 (VIN), U5.1 (IN)
/V3V3_AON: C5.1, J2.3, JP1.2, R7.1, R8.1, R10.1, R11.1, R12.1, R13.1, R20.1, TP3.1
/V3V3_SW: C6.1, J2.4, JP2.2, TP4.1
/WAKE: D2.1 (K1), J2.9, R9.1, R14.1, TP14.1

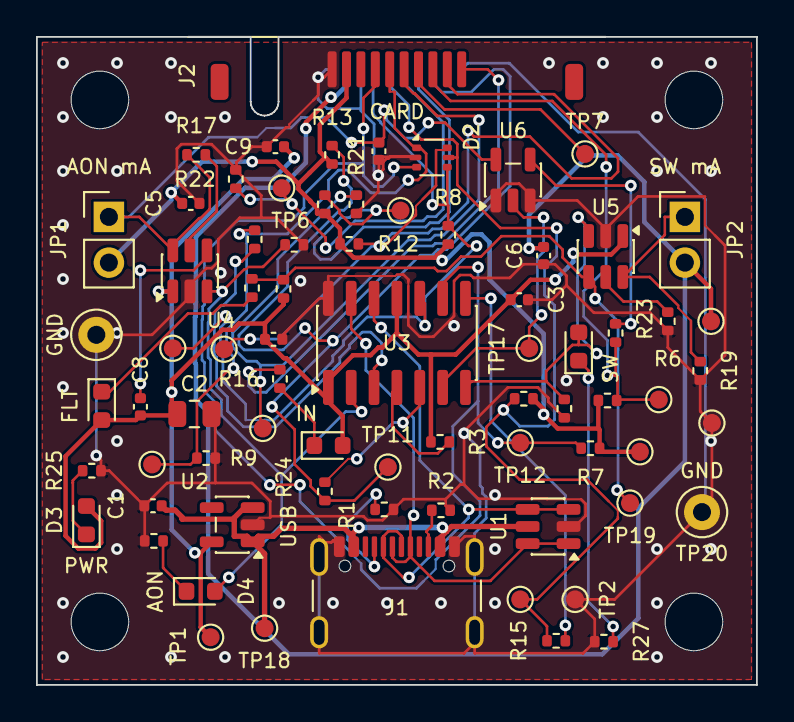
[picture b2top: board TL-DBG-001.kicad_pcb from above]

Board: 2 copper layers, 40.0 x 36.0 mm, 78 parts (0 on the bottom side), 40 nets.

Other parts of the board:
H1, H2, H3, H4: mounting hole; MountingHole_3.2mm_M3

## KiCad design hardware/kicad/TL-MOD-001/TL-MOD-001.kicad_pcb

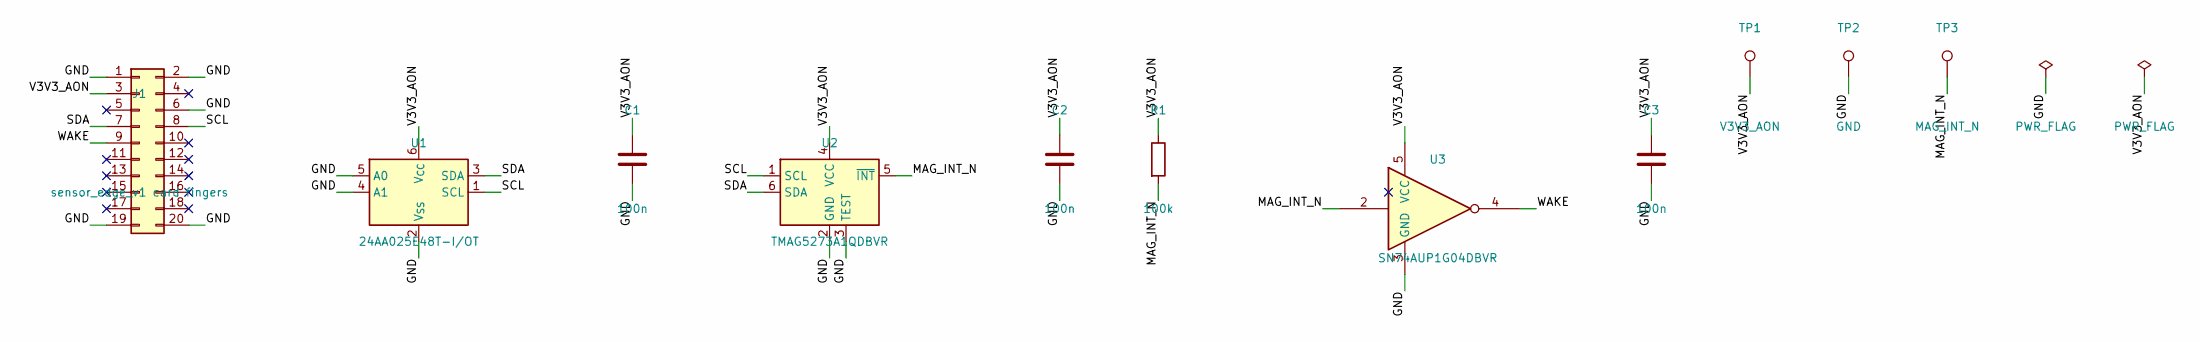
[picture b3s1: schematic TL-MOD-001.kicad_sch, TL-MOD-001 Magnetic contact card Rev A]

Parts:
C1, C2, C3: 100n; C_0402_1005Metric
J1: sensor_edge_v1 card fingers; CardEdge_sensor_edge_v1_2x10_P0.8mm
R1: 100k; R_0402_1005Metric
TP1: V3V3_AON; TestPoint_Pad_D1.0mm
TP2: GND; TestPoint_Pad_D1.0mm
TP3: MAG_INT_N; TestPoint_Pad_D1.0mm
U1: 24AA025E48T-I/OT; SOT-23-6
U2: TMAG5273A1QDBVR; SOT-23-6
U3: SN74AUP1G04DBVR; SOT-23-5

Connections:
/GND: C1.2, C2.2, C3.2, J1.1, J1.2, J1.6, J1.19, J1.20, TP2.1, U1.2 (V_{SS}), U1.4 (A1), U1.5 (A0), U2.2 (GND), U2.3 (TEST), U3.3 (GND)
/MAG_INT_N: R1.2, TP3.1, U2.5 (~INT), U3.2
/SCL: J1.8, U1.1 (SCL), U2.1 (SCL)
/SDA: J1.7, U1.3 (SDA), U2.6 (SDA)
/V3V3_AON: C1.1, C2.1, C3.1, J1.3, R1.1, TP1.1, U1.6 (V_{CC}), U2.4 (VCC), U3.5 (VCC)
/WAKE: J1.9, U3.4
